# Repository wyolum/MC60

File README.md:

# MC60
break out board for Quectel MC60 Ultra-small LCC Quad-band GSM/GPRS/GNSS Module

http://www.quectel.com/product/mc60.htm

License
-------
[CERN Open Hardware Licence v1.2 ]

[CERN Open Hardware Licence v1.2 ]:http://www.ohwr.org/attachments/2388/cern_ohl_v_1_2.txt

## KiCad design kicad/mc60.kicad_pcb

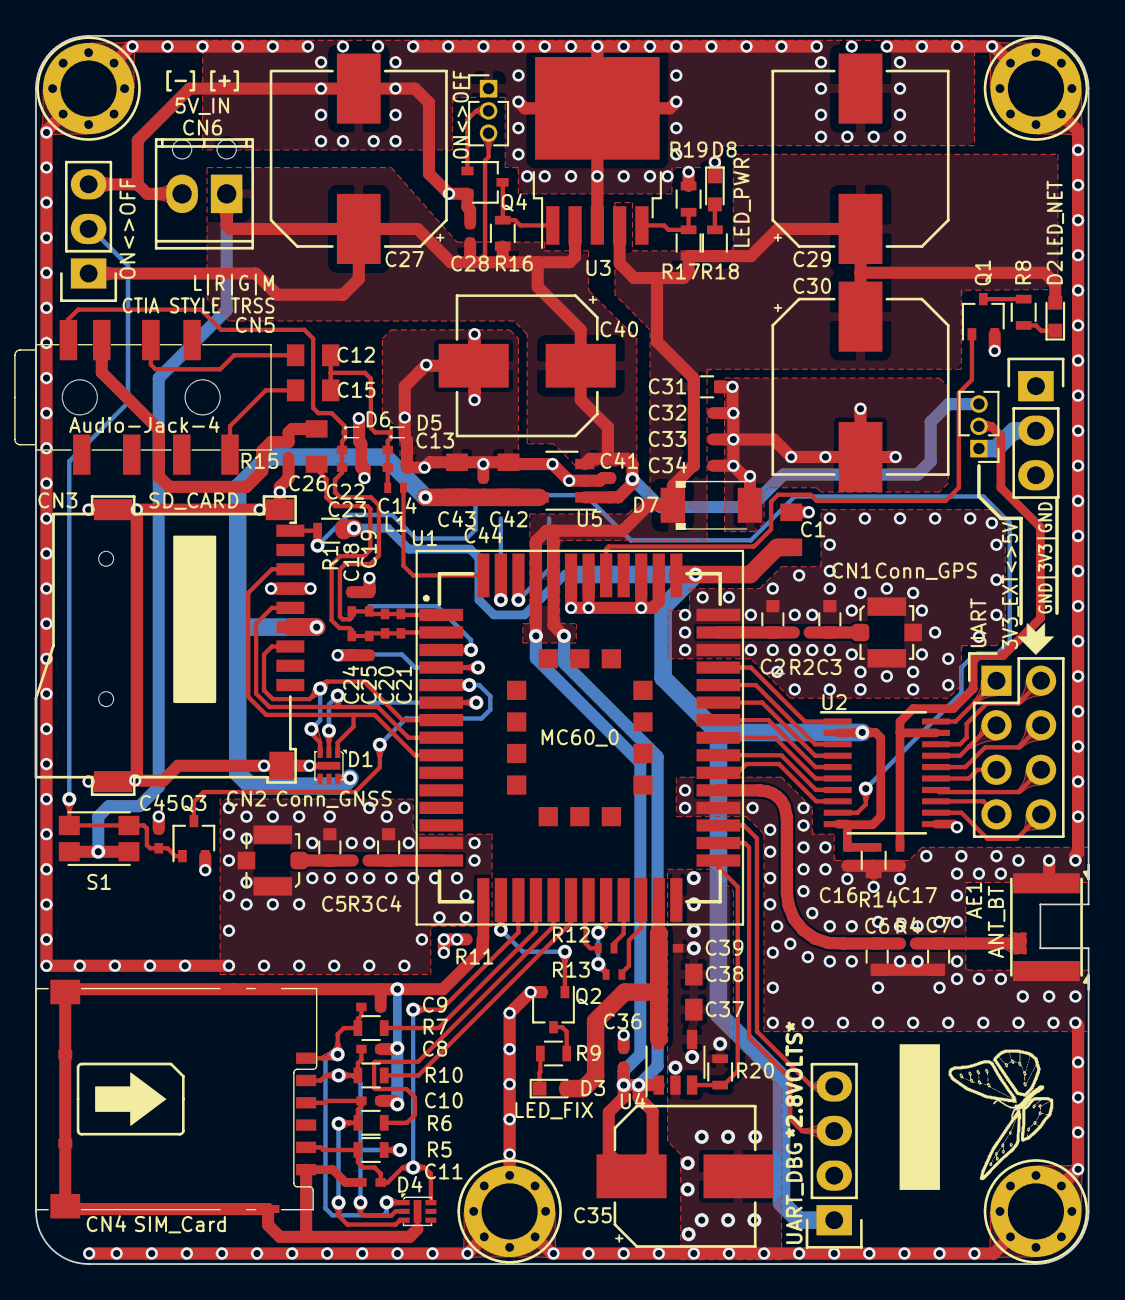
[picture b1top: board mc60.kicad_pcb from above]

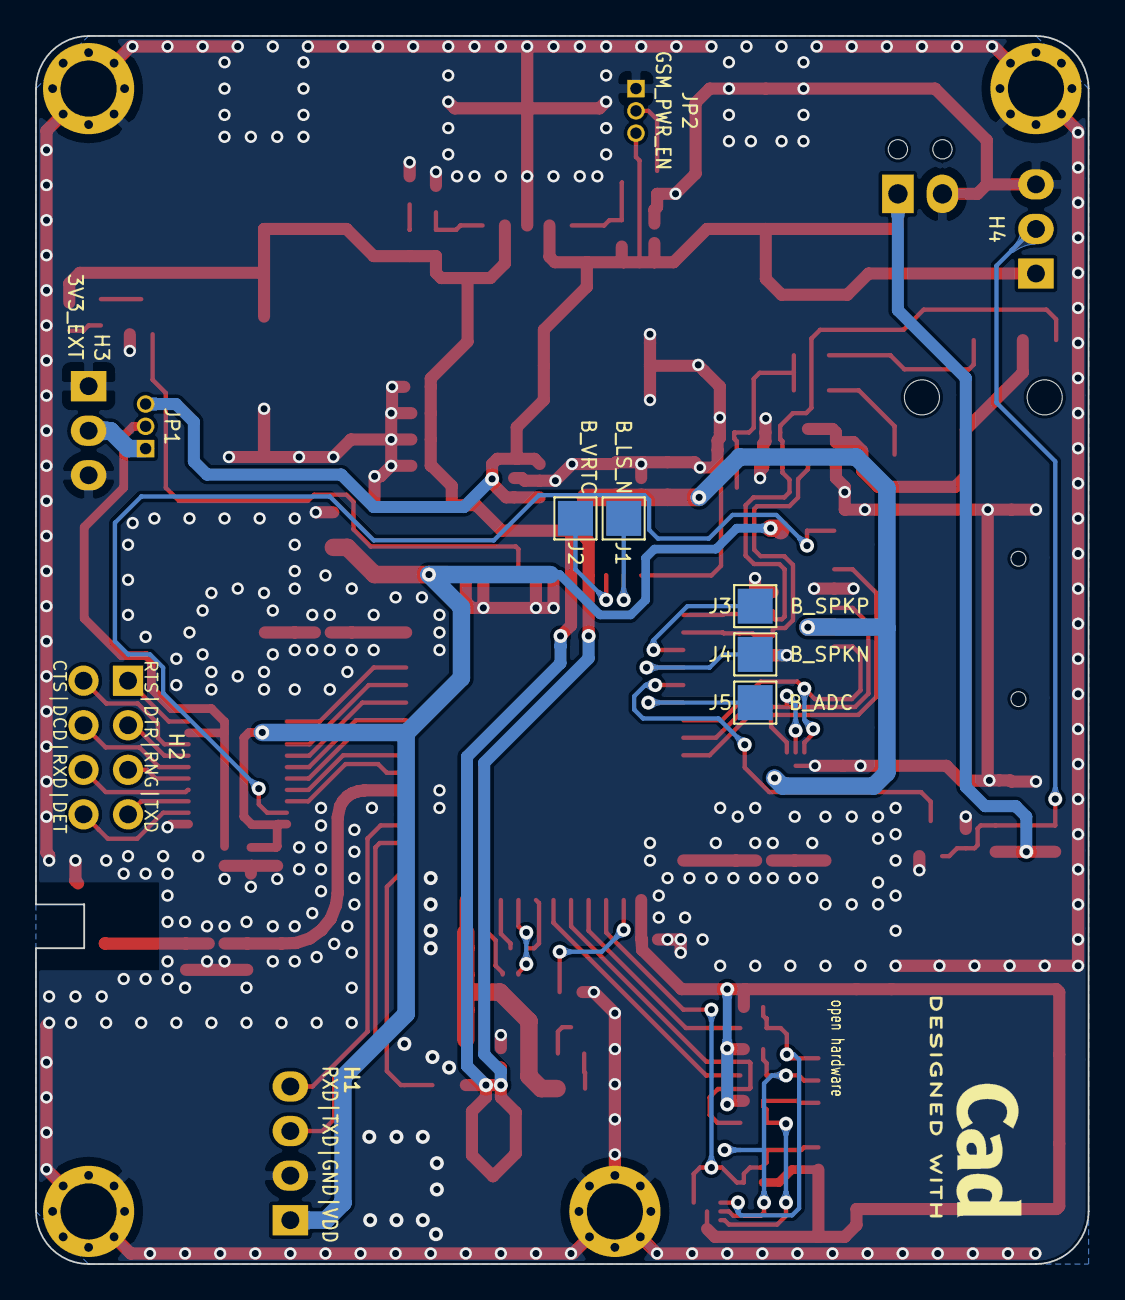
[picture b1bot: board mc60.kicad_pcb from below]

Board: 2 copper layers, 60.0 x 70.0 mm, 109 parts (7 on the bottom side), 72 nets.

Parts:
AE1: ANT_BT; ant_bt_inpaq5036
C1, C37, C42: 4u7; C_0805
C2, C3, C4, C5, C6, C7: 10pF_DNP; C_0603
C8, C9, C10, C11, C13, C18, C20, C22, C24, C33, C45: 33pF; C_0402_NoSilk
C12, C15, C26, C38, C43: 10uF; C_0805
C14, C19, C21, C23, C25, C34: 10pF; C_0402_NoSilk
C16, C17, C28, C32, C36, C39, C41, C44: 100nF; C_0402_NoSilk
C27, C29, C30: 470uF; CP_Elec_10x10
C31: 1uF; C_0603
C35, C40: 100uF; CP_Elec_8x10.5
CN1: Conn_GPS; Molex_Microcoaxial_RF
CN2: Conn_GNSS; Molex_Microcoaxial_RF
CN3: SD_CARD; microsd-9-suntech-ST-TF-003A
CN4: SIM_Card; conn_microSIM_320100004
CN5: Audio-Jack-4; AUDIO8P-SMD-3.5-14.5X6X5MM
CN6: 5V_IN; conn_screw_2.54mm_2pol
D1, D4: RClamp0854P.TCT; SLP1616P6
D2: LED_NET; LED_0603
D3: LED_FIX; LED_0603
D5, D6: ESD9B5.0ST5G; D_SOD-923
D7: PDZVTR5.1B; D_SOD-128
D8: LED_PWR; LED_0603
G1: OSHW; Logo_silk_OSHW_6x6mm_mask
G2: KiCad; KiCad-Logo3_6mm_SilkScreen
G3: LOGO_WL; logo_wyo3
H1: UART_DBG; Pin_Header_Straight_1x04
H2: UART; Pin_Header_Straight_2x04
H3: 3V3_EXT; Pin_Header_Straight_1x03
H4: ON<>OFF; Pin_Header_Straight_1x03
J1: B_LS_N; Test_Point_Pad_2.0x2.0mm
J2: B_VRTC; Test_Point_Pad_2.0x2.0mm
J3: B_SPKP; Test_Point_Pad_2.0x2.0mm
J4: B_SPKN; Test_Point_Pad_2.0x2.0mm
J5: B_ADC; Test_Point_Pad_2.0x2.0mm
JP1: 3V3_EXT<>5V; Pin_Header_Straight_1x03_Pitch1.27mm
JP2: GSM_PWR_EN; Pin_Header_Straight_1x03_Pitch1.27mm
L1: 0E; R_0402_NoSilk
Q1, Q2, Q3: DTC114E; SOT-323_SC-70
Q4: DTC143ZUA; SOT-323_SC-70
R1, R5: 100k; R_0603
R2, R3, R4, R11, R12, R13, R15: 0E; R_0402_NoSilk
R6, R7, R10: 22E; R_0603
R8, R18: 390E; R_0603
R9: 270E; R_0603
R14: 10k; R_0603
R16: 51k; R_0603
R17: 124k; R_0603
R19: 56k; R_0603
R20: 47k; R_0603
S1: SW-ON; SW_SPST_WS_TASV
SC1, SC2, SC3, SC4: SCREW; mtg_hole_3mm_vias_2
U1: MC60_0; XCVR_MC60
U2: TXB0108PWR; TSSOP-20_4.4x6.5mm_Pitch0.65mm
U3: MIC29302; TO-252-5_TabPin3
U4: LP5907-3V3; SOT-23-5
U5: LP5907-2V8; SOT-23-5

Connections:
/1PPS: Q2.1, U1.17
/2V8_SD: C42.1, C43.1, C44.1, CN3.4, D1.6, U5.5
/3V3_EXT: H3.2, JP1.1
/ADC: J5.1, U1.6
/ANT_BT: C6.2, R4.2, U1.32
/ANT_GNSS: C4.2, R3.2, U1.15
/ANT_GPS: C2.2, R2.2, U1.41
/CTS: H2.2, U2.18
/CTS>: U1.38, U2.3
/DBG_RXD: H1.4, U1.30
/DBG_TXD: H1.3, U1.29
/DCD: H2.4, U2.16
/DCD>: U1.36, U2.5
/DTR: H2.3, U2.17
/DTR>: U1.37, U2.4
/GNSSVCC: C37.1, C38.1, C39.1, D3.2, U1.26, U4.5
/GNSS_VCC_EN: R20.1, U1.28, U4.3
/GSM_PWR_EN: JP2.2, Q4.1
/LEFT: C15.2, CN5.4
/LOUD_SPKN: J1.1, U1.53
/LOUD_SPKP: L1.1, U1.54
/L_SP: C12.1, C13.2, C14.2, C15.1, D5.1, L1.2
/MIC_N: C20.1, C21.1, C24.2, C25.2, C26.1, U1.2
/MIC_P: C18.1, C19.1, C20.2, C21.2, C22.2, C23.2, CN5.1, D6.1, U1.1
/NETLIGHT: Q1.1, U1.47
/PWRKEY: Q3.3, U1.5
/RIGHT: C12.2, CN5.3
/RING: H2.5, U2.15
/RING>: U1.35, U2.6
/RST: C45.2, H4.2, Q3.1, S1.1
/RTS: H2.1, U2.20
/RTS>: U1.39, U2.1
/RXD: H2.6, U2.14
/RXD>: U1.34, U2.7
/RXD_AUX: R12.1, U1.24
/RXD_G: R13.2, U1.23
/SD_CLK: CN3.5, D1.2, U1.8
/SD_CMD: CN3.3, D1.3, U1.7
/SD_DAT: CN3.7, D1.1, U1.9
/SD_DET: H2.8, U2.12
/SD_DET>: CN3.9, R1.2, U2.9
/SIM1_VDD: C11.2, CN4.P1, D4.6, R5.1, U1.18
/SIMCLK: C9.2, CN4.P3, D4.1, R7.1
/SIMDAT: C8.2, CN4.P7, D4.2, R5.2, R10.1
/SIMRST: C10.2, CN4.P2, D4.3, R6.1
/SIM_CLK: R7.2, U1.19
/SIM_DAT: R10.2, U1.21
/SIM_RST: R6.2, U1.20
/SPKN: J4.1, U1.4
/SPKP: J3.1, U1.3
/TXD: H2.7, U2.13
/TXD>: U1.33, U2.8
/TXD_AUX: R13.1, U1.25
/TXD_G: R12.2, U1.22
/VCCB: C17.1, JP1.2, U2.19
/VDD_EXT: C1.1, C16.1, H1.1, R1.1, R14.1, U1.43, U2.2, U2.10
/VRTC: J2.1, U1.52
GND: AE1.1, C1.2, C2.1, C3.1, C4.1, C5.1, C6.1, C7.1, C13.1, C14.1, C16.2, C17.2, C18.2, C19.2, C22.1, C23.1, C24.1, C25.1, C27.2, C28.2, C29.2, C30.2, C31.2, C32.2, C33.2, C34.2, C35.2, C36.2, C37.2, C38.2, C39.2, C40.2, C41.2, C42.2, C43.2, C44.2, C45.1, CN1.2, CN2.2, CN3.6, CN3.G1, CN3.G2, CN3.G3, CN3.G4, CN6.2, D1.7, D5.2, D6.2, D7.2, D8.1, H1.2, H3.1, H3.3, H4.3, JP2.1, Q1.2, Q2.2, Q3.2, Q4.2, R11.2, R14.2, R15.2, R19.2, R20.2, SC1.1, SC2.1, SC3.1, SC4.1, U1.14, U1.27, U1.31, U1.40, U1.42, U1.44, U1.45, U1.48, U1.49, U2.11, U3.3, U4.2, U4.4, U5.2, U5.4
GNDD: C8.1, C9.1, C10.1, C11.1, CN4.G1, CN4.G2, CN4.G3, CN4.G4, CN4.G5, CN4.G6, CN4.G7, CN4.G8, CN4.P5, D4.7, R11.1, U1.16
GNDREF: C26.2, CN5.2, R15.1
unnamed: AE1.2, C7.2, R4.1
unnamed: C3.2, CN1.1, R2.1
unnamed: C5.2, CN2.1, R3.1
unnamed: D2.1, R8.1
unnamed: D3.1, R9.1
unnamed: D8.2, R18.2
unnamed: Q1.3, R8.2
unnamed: Q2.3, R9.2
unnamed: Q4.3, R16.2, U3.1
unnamed: R17.2, R19.1, U3.5
VBAT: C29.1, C30.1, C31.1, C32.1, C33.1, C34.1, C35.1, C36.1, D2.2, D7.1, R17.1, R18.1, U1.50, U1.51, U3.4, U4.1
VDD: C27.1, C28.1, C40.1, C41.1, CN6.1, H4.1, JP1.3, JP2.3, R16.1, S1.2, U3.2, U5.1, U5.3

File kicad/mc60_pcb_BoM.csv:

"Id";"Designator";"Package";"Quantity";"Designation";"Supplier and ref";
1;"SC1,SC2,SC3,SC4";"mtg_hole_3mm_vias_2";4;"SCREW";;;
2;"G2";"KiCad-Logo3_6mm_SilkScreen";1;"KiCad";;;
3;"S1";"SW_SPST_WS_TASV";1;"SW-ON";;;
4;"G3";"logo_wyo3";1;"LOGO_WL";;;
5;"G1";"Logo_silk_OSHW_6x6mm_mask";1;"OSHW";;;
6;"JP1";"Pin_Header_Straight_1x03_Pitch1.27mm";1;"3V3_EXT<>5V";;;
7;"JP2";"Pin_Header_Straight_1x03_Pitch1.27mm";1;"GSM_PWR_EN";;;
8;"Q3,Q1,Q2";"SOT-323_SC-70";3;"DTC114E";;;
9;"C45,C9,C8,C10,C11,C13,C18,C20,C22,C24,C33";"C_0402_NoSilk";11;"33pF";;;
10;"R2,R3,R4,R11,R12,R13,R15,L1";"R_0402_NoSilk";8;"0E";;;
11;"C35,C40";"CP_Elec_8x10.5";2;"100uF";;;
12;"C30,C27,C29";"CP_Elec_10x10";3;"470uF";;;
13;"C1,C37,C42";"C_0805";3;"4u7";;;
14;"U1";"XCVR_MC60";1;"MC60_0";;;
15;"AE1";"ant_bt_inpaq5036";1;"ANT_BT";;;
16;"J1";"Test_Point_Pad_2.0x2.0mm";1;"B_LS_N";;;
17;"J2";"Test_Point_Pad_2.0x2.0mm";1;"B_VRTC";;;
18;"J3";"Test_Point_Pad_2.0x2.0mm";1;"B_SPKP";;;
19;"J4";"Test_Point_Pad_2.0x2.0mm";1;"B_SPKN";;;
20;"J5";"Test_Point_Pad_2.0x2.0mm";1;"B_ADC";;;
21;"H4";"Pin_Header_Straight_1x03";1;"ON<>OFF";;;
22;"C6,C2,C3,C4,C5,C7";"C_0603";6;"10pF_DNP";;;
23;"C12,C15,C26,C38,C43";"C_0805";5;"10uF";;;
24;"C31";"C_0603";1;"1uF";;;
25;"CN3";"microsd-9-suntech-ST-TF-003A";1;"SD_CARD";;;
26;"CN4";"conn_microSIM_320100004";1;"SIM_Card";;;
27;"CN5";"AUDIO8P-SMD-3.5-14.5X6X5MM";1;"Audio-Jack-4";;;
28;"D1,D4";"SLP1616P6";2;"RClamp0854P.TCT";;;
29;"D2";"LED_0603";1;"LED_NET";;;
30;"D3";"LED_0603";1;"LED_FIX";;;
31;"D5,D6";"D_SOD-923";2;"ESD9B5.0ST5G";;;
32;"D7";"D_SOD-128";1;"PDZVTR5.1B";;;
33;"D8";"LED_0603";1;"LED_PWR";;;
34;"H2";"Pin_Header_Straight_2x04";1;"UART";;;
35;"Q4";"SOT-323_SC-70";1;"DTC143ZUA";;;
36;"R1,R5";"R_0603";2;"100k";;;
37;"R6,R7,R10";"R_0603";3;"22E";;;
38;"R8,R18";"R_0603";2;"390E";;;
39;"R9";"R_0603";1;"270E";;;
40;"R14";"R_0603";1;"10k";;;
41;"R16";"R_0603";1;"51k";;;
42;"R17";"R_0603";1;"124k";;;
43;"R19";"R_0603";1;"56k";;;
44;"R20";"R_0603";1;"47k";;;
45;"U2";"TSSOP-20_4.4x6.5mm_Pitch0.65mm";1;"TXB0108PWR";;;
46;"U3";"TO-252-5_TabPin3";1;"MIC29302";;;
47;"U4";"SOT-23-5";1;"LP5907-3V3";;;
48;"U5";"SOT-23-5";1;"LP5907-2V8";;;
49;"C14,C19,C21,C23,C25,C34";"C_0402_NoSilk";6;"10pF";;;
50;"C16,C17,C28,C32,C36,C39,C41,C44";"C_0402_NoSilk";8;"100nF";;;
51;"CN1";"Molex_Microcoaxial_RF";1;"Conn_GPS";;;
52;"CN2";"Molex_Microcoaxial_RF";1;"Conn_GNSS";;;
53;"CN6";"conn_screw_2.54mm_2pol";1;"5V_IN";;;
54;"H3";"Pin_Header_Straight_1x03";1;"3V3_EXT";;;
55;"H1";"Pin_Header_Straight_1x04";1;"UART_DBG";;;

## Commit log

2018-04-08 added datasheets
2018-04-08 schematic wip
2018-04-23 layout WIP
2018-05-11 Update README.md
    added images
2018-05-13 UART header update, added freeite bead on Loudspeaker, added Cap for Switch
2018-05-19 board layout WIP
2018-05-19 board layout, WiP
2019-06-25 gerbers for first prototypes
